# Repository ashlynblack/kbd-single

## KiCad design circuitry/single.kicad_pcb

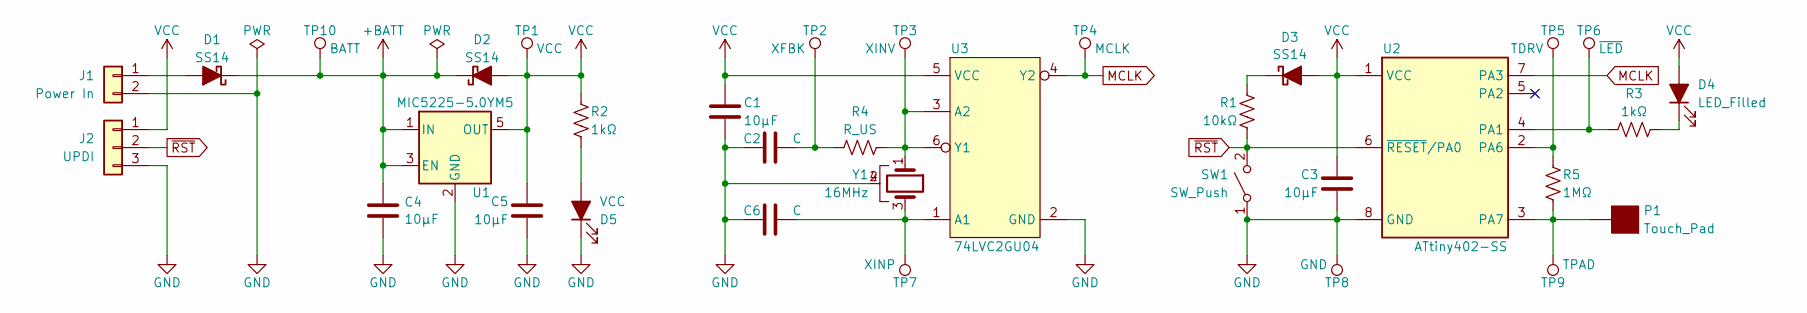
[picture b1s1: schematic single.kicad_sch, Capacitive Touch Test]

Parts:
C1, C3, C4, C5: 10µF; C_1206_3216Metric_Pad1.33x1.80mm_HandSolder
C2, C6: C; C_0805_2012Metric_Pad1.18x1.45mm_HandSolder
D1, D2, D3: SS14; D_SMA
D4, D5: LED_Filled; LED_1206_3216Metric_Pad1.42x1.75mm_HandSolder
J1: Conn_01x02; JST_XH_S2B-XH-A-1_1x02_P2.50mm_Horizontal
J2: Conn_01x03; JST_XH_S3B-XH-A-1_1x03_P2.50mm_Horizontal
P1: Touch_Pad
R1: 10kΩ; R_0805_2012Metric_Pad1.20x1.40mm_HandSolder
R2, R3: 1kΩ; R_0805_2012Metric_Pad1.20x1.40mm_HandSolder
R4: R_US; R_0805_2012Metric_Pad1.20x1.40mm_HandSolder
R5: 1MΩ; R_0805_2012Metric_Pad1.20x1.40mm_HandSolder; Tolerance 0.1%
SW1: SW_Push; SW_PUSH_6mm_H5mm
TP1, TP2, TP3, TP4, TP5, TP6, TP7, TP8, TP9, TP10: TestPoint; TEST-TH_Loop_D2.40mm_Drill0.9mm_Beaded
U1: MIC5225-5.0YM5; SOT-23-5
U2: ATtiny402-SS; SOIC-8_3.9x4.9mm_P1.27mm
U3: 74LVC2GU04; SOT-23-6_Handsoldering
Y1: 16MHz; Crystal_SMD_3225-4Pin_3.2x2.5mm_HandSoldering

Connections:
+BATT: C4.1, D1.1 (K), D2.1 (K), TP10.1, U1.1 (IN), U1.3 (EN)
GND: C1.2, C2.1, C3.2, C4.2, C5.2, C6.1, D5.1 (K), J1.2, J2.3, SW1.1 (A), TP8.1, U1.2 (GND), U2.8 (GND), U3.2 (GND), Y1.2, Y1.4
MCLK: TP4.1, U2.7 (PA3), U3.4 (Y2)
unnamed: C2.2, R4.1, TP2.1
unnamed: D1.2 (A), J1.1
unnamed: D3.1 (K), R1.1
unnamed: D4.1 (K), R3.2
unnamed: D5.2 (A), R2.2
unnamed: R3.1, TP6.1, U2.4 (PA1)
unnamed: R5.1, TP5.1, U2.2 (PA6)
unnamed: P1.1, R5.2, TP9.1, U2.3 (PA7)
unnamed: C6.2, TP7.1, U3.1 (A1), Y1.3
unnamed: R4.2, TP3.1, U3.3 (A2), U3.6 (Y1), Y1.1
VCC: C1.1, C3.1, C5.1, D2.2 (A), D3.2 (A), D4.2 (A), J2.1, R2.1, TP1.1, U1.5 (OUT), U2.1 (VCC), U3.5 (VCC)
~RST: J2.2, R1.2, SW1.2 (B), U2.6 (~RESET/PA0)

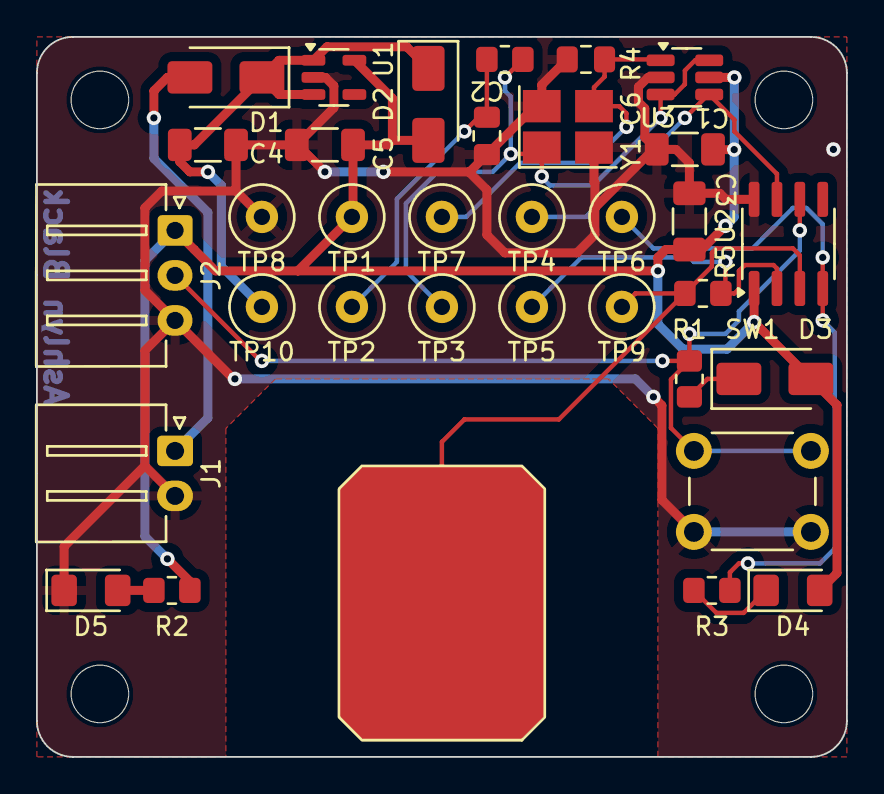
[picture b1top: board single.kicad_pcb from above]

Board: 2 copper layers, 45.0 x 40.0 mm, 34 parts (0 on the bottom side), 15 nets.

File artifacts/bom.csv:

"Reference","Value","Footprint","Qty"
"C1,C3,C4,C5","10µF","Capacitor_SMD:C_1206_3216Metric_Pad1.33x1.80mm_HandSolder","4"
"C2,C6","C","Capacitor_SMD:C_0805_2012Metric_Pad1.18x1.45mm_HandSolder","2"
"D1,D2,D3","SS14","Diode_SMD:D_SMA_Handsoldering","3"
"D4,D5","LED_Filled","LED_SMD:LED_1206_3216Metric_Pad1.42x1.75mm_HandSolder","2"
"J1","Conn_01x02","Connector_JST:JST_XH_S2B-XH-A-1_1x02_P2.50mm_Horizontal","1"
"J2","Conn_01x03","Connector_JST:JST_XH_S3B-XH-A-1_1x03_P2.50mm_Horizontal","1"
"P1","Touch_Pad","Single:Touch_Pad","1"
"R1","10kΩ","Resistor_SMD:R_0805_2012Metric_Pad1.20x1.40mm_HandSolder","1"
"R2,R3","1kΩ","Resistor_SMD:R_0805_2012Metric_Pad1.20x1.40mm_HandSolder","2"
"R4","R_US","Resistor_SMD:R_0805_2012Metric_Pad1.20x1.40mm_HandSolder","1"
"R5","1MΩ","Resistor_SMD:R_0805_2012Metric_Pad1.20x1.40mm_HandSolder","1"
"SW1","SW_Push","Button_Switch_THT:SW_PUSH_6mm_H5mm","1"
"TP1,TP2,TP3,TP4,TP5,TP6,TP7,TP8,TP9","TestPoint","Single:TEST-TH_Loop_D2.40mm_Drill0.9mm_Beaded","9"
"U1","MIC5225-5.0YM5","Package_TO_SOT_SMD:SOT-23-5","1"
"U2","ATtiny402-SS","Package_SO:SOIC-8_3.9x4.9mm_P1.27mm","1"
"U3","74LVC2GU04","Package_TO_SOT_SMD:SOT-23-6_Handsoldering","1"
"Y1","16MHz","Crystal:Crystal_SMD_3225-4Pin_3.2x2.5mm_HandSoldering","1"

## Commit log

2024-07-11 temp
2024-07-27 Created Git ignore list.
2024-07-27 Tracked PDF, ZIP, JPG and PNG files with Git LFS.
2024-07-27 Updated datasheets.
2024-07-27 Completed schematic and layout.
2024-07-27 Generated artifacts.
